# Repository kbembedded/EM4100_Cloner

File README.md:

EM4100 Cloner
=================

This RFID project is the second iteration of the RFID board for DEF CON's DarkNet game.  This project is based on the OPEN RFID tag with resources pulled from t4f.org and kukata86.com.  Envelope detector credit to multiple people listed here: http://playground.arduino.cc/Main/DIYRFIDReader

This project is to create a battery powered RFID cloner that is compatible with LF 125kHz RFID tags, a.k.a. EM4100.  There are 16 slots each able to store a 5 ID.  This device does not clone a tag and reprogram another, it is able to read and clone a tag and then turn around to emulate it to a proper transponder.  There is also a mechanism to manually program an ID to the device via the button and DIP switch.  Any of the 16 slots can have a cloned ID saved, a manually input ID saved, and an ID replayed from.

2023-05-06: I've discovered that Microchip has radically changed their assembler system. This will not compile under current MPLAB X IDEs, but should work on the older v3.50 or v3.55 (I think is what was originally used). They can still be found here: [https://www.microchip.com/en-us/tools-resources/archives/mplab-ecosystem#MPLAB%20XC%20Compiler%20Archives](https://www.microchip.com/en-us/tools-resources/archives/mplab-ecosystem#MPLAB%20XC%20Compiler%20Archives) If that link ever goes stale, well, good luck.

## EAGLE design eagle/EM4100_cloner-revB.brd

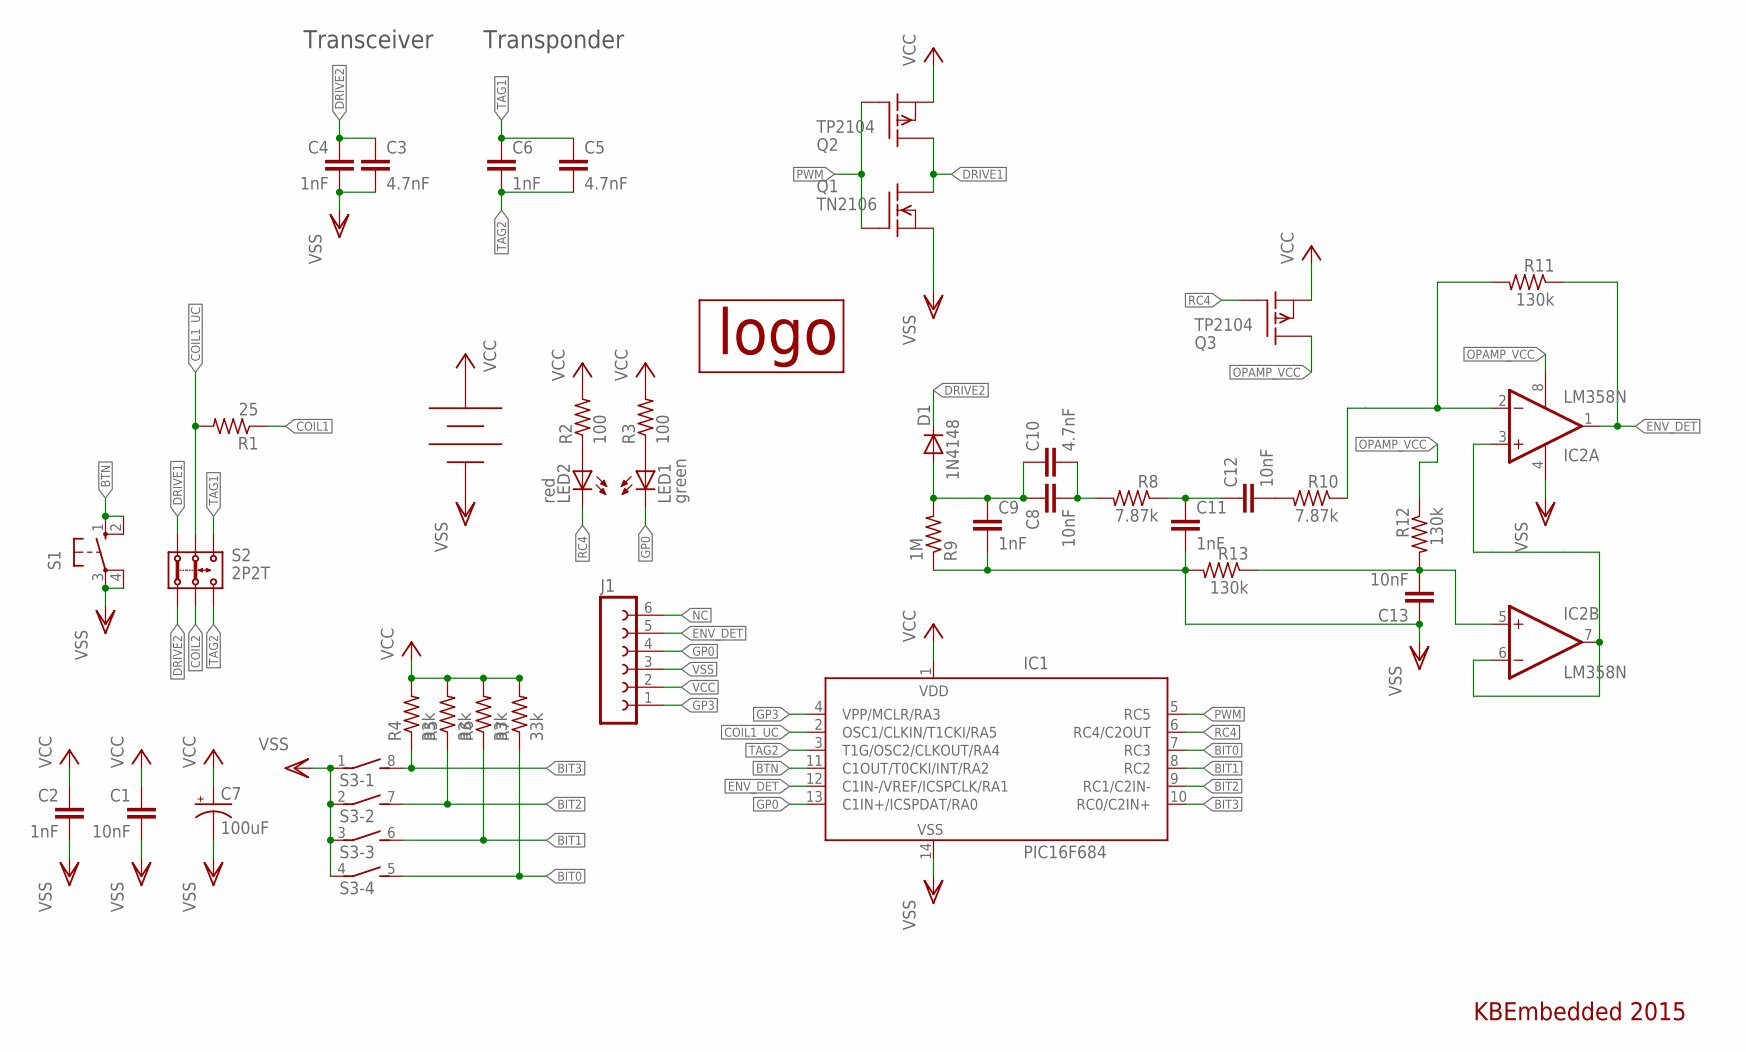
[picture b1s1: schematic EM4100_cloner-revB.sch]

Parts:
BT1: BAT-HLD-001-THM
C1, C8, C12, C13: 10nF; C050-024X044
C2, C4, C6, C9, C11: 1nF; C050-024X044
C3, C5, C10: 4.7nF; C050-024X044
C7: 100uF; E2,5-6E
D1: 1N4148; D-5
IC1: PIC16F684; DIL14
IC2: LM358N; DIL08
J1: FE06-1; FE06
LED1: green; LED3MM
LED2: red; LED3MM
Q1: TN2106; TO-92
Q2, Q3: TP2104; TO-92
R1: 25; 0204/7
R2, R3: 100; 0204/7
R4, R5, R6, R7: 33k; 0204/7
R8, R10: 7.87k; 0204/7
R9: 1M; 0204/7
R11, R12, R13: 130k; 0204/7
S1: 10-XX; B3F-10XX
S2: 2P2T
S3: DIP04S
U$1: KBELOGO-SILK

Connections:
BIT0: IC1.7 (RC3), R7.1, S3.5 (2)
BIT1: IC1.8 (RC2), R6.1, S3.6 (2)
BIT2: IC1.9 (RC1/C2IN-), R5.1, S3.7 (2)
BIT3: IC1.10 (RC0/C2IN+), R4.1, S3.8 (2)
BTN: IC1.11 (C1OUT/T0CKI/INT/RA2), S1.1 (S), S1.2 (S1)
COIL1: R1.1
COIL1_UC: IC1.2 (OSC1/CLKIN/T1CKI/RA5), R1.2, S2.2.1
COIL2: S2.2.2
DRIVE1: Q1.3 (D), Q2.3 (D), S2.1.1
DRIVE2: C3.1, C4.1, D1.C, S2.1.2
ENV_DET: IC1.12 (C1IN-/VREF/ICSPCLK/RA1), IC2.1 (OUT), J1.5, R11.1
GP0: IC1.13 (C1IN+/ICSPDAT/RA0), J1.4, LED1.K (C)
GP3: IC1.4 (VPP/MCLR/RA3), J1.1
unnamed: LED2.A, R2.1
unnamed: LED1.A, R3.1
unnamed: C8.1, C9.1, C10.1, D1.A, R9.2
unnamed: C8.2, C10.2, R8.2
unnamed: C11.1, C12.1, R8.1
unnamed: C12.2, R10.2
unnamed: IC2.3 (+IN), IC2.6 (-IN), IC2.7 (OUT)
unnamed: C13.2, IC2.5 (+IN), R12.2, R13.1
unnamed: IC2.2 (-IN), R10.1, R11.2
NC: J1.6
OPAMP_VCC: IC2.8 (V+), Q3.3 (D), R12.1
PWM: IC1.5 (RC5), Q1.2 (G), Q2.2 (G)
RC4: IC1.6 (RC4/C2OUT), LED2.K (C), Q3.2 (G)
TAG1: C5.1, C6.1, S2.3.1
TAG2: C5.2, C6.2, IC1.3 (T1G/OSC2/CLKOUT/RA4), S2.3.2
VCC: BT1.+@0 (VCC), BT1.+@1 (VCC), BT1.+@2 (VCC), BT1.+@3 (VCC), C1.1, C2.1, C7.+, IC1.1 (VDD), J1.2, Q2.1 (S), Q3.1 (S), R2.2, R3.2, R4.2, R5.2, R6.2, R7.2
VSS: BT1.- (VSS), C1.2, C2.2, C3.2, C4.2, C7.-, C9.2, C11.2, C13.1, IC1.14 (VSS), IC2.4 (V-), J1.3, Q1.1 (S), R9.1, R13.2, S1.3, S1.4 (P1), S3.1, S3.2 (1), S3.3 (1), S3.4 (1)

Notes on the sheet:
Transceiver
Transponder
KBEmbedded 2015

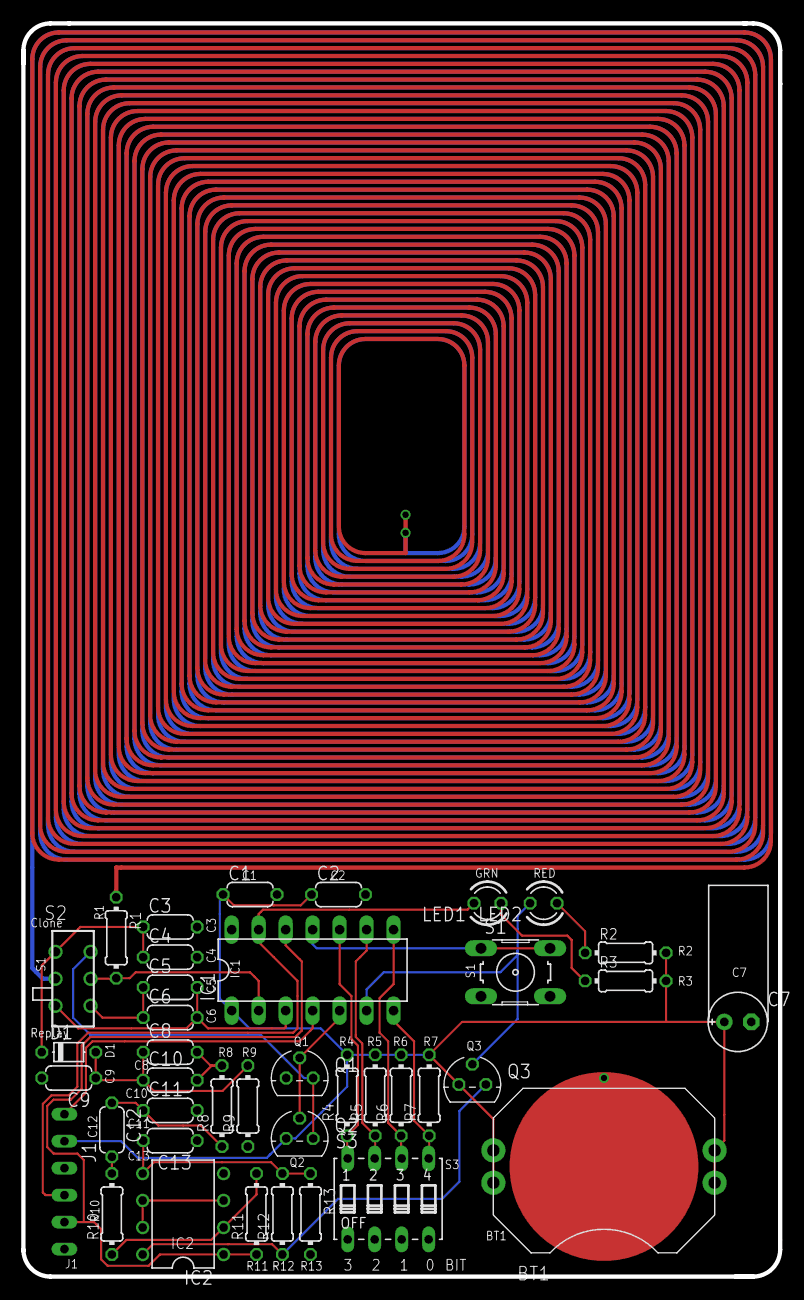
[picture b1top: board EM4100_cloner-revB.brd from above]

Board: 2 copper layers, 71.2 x 118.0 mm, 41 parts (0 on the bottom side), 27 nets.

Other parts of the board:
U$2: DN_LOGO

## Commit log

2015-08-05 Added build instructions
2015-08-05 Added series resistors in a couple of places on the readerstation that I originally missed
2023-05-07 README: Update with tool notice
